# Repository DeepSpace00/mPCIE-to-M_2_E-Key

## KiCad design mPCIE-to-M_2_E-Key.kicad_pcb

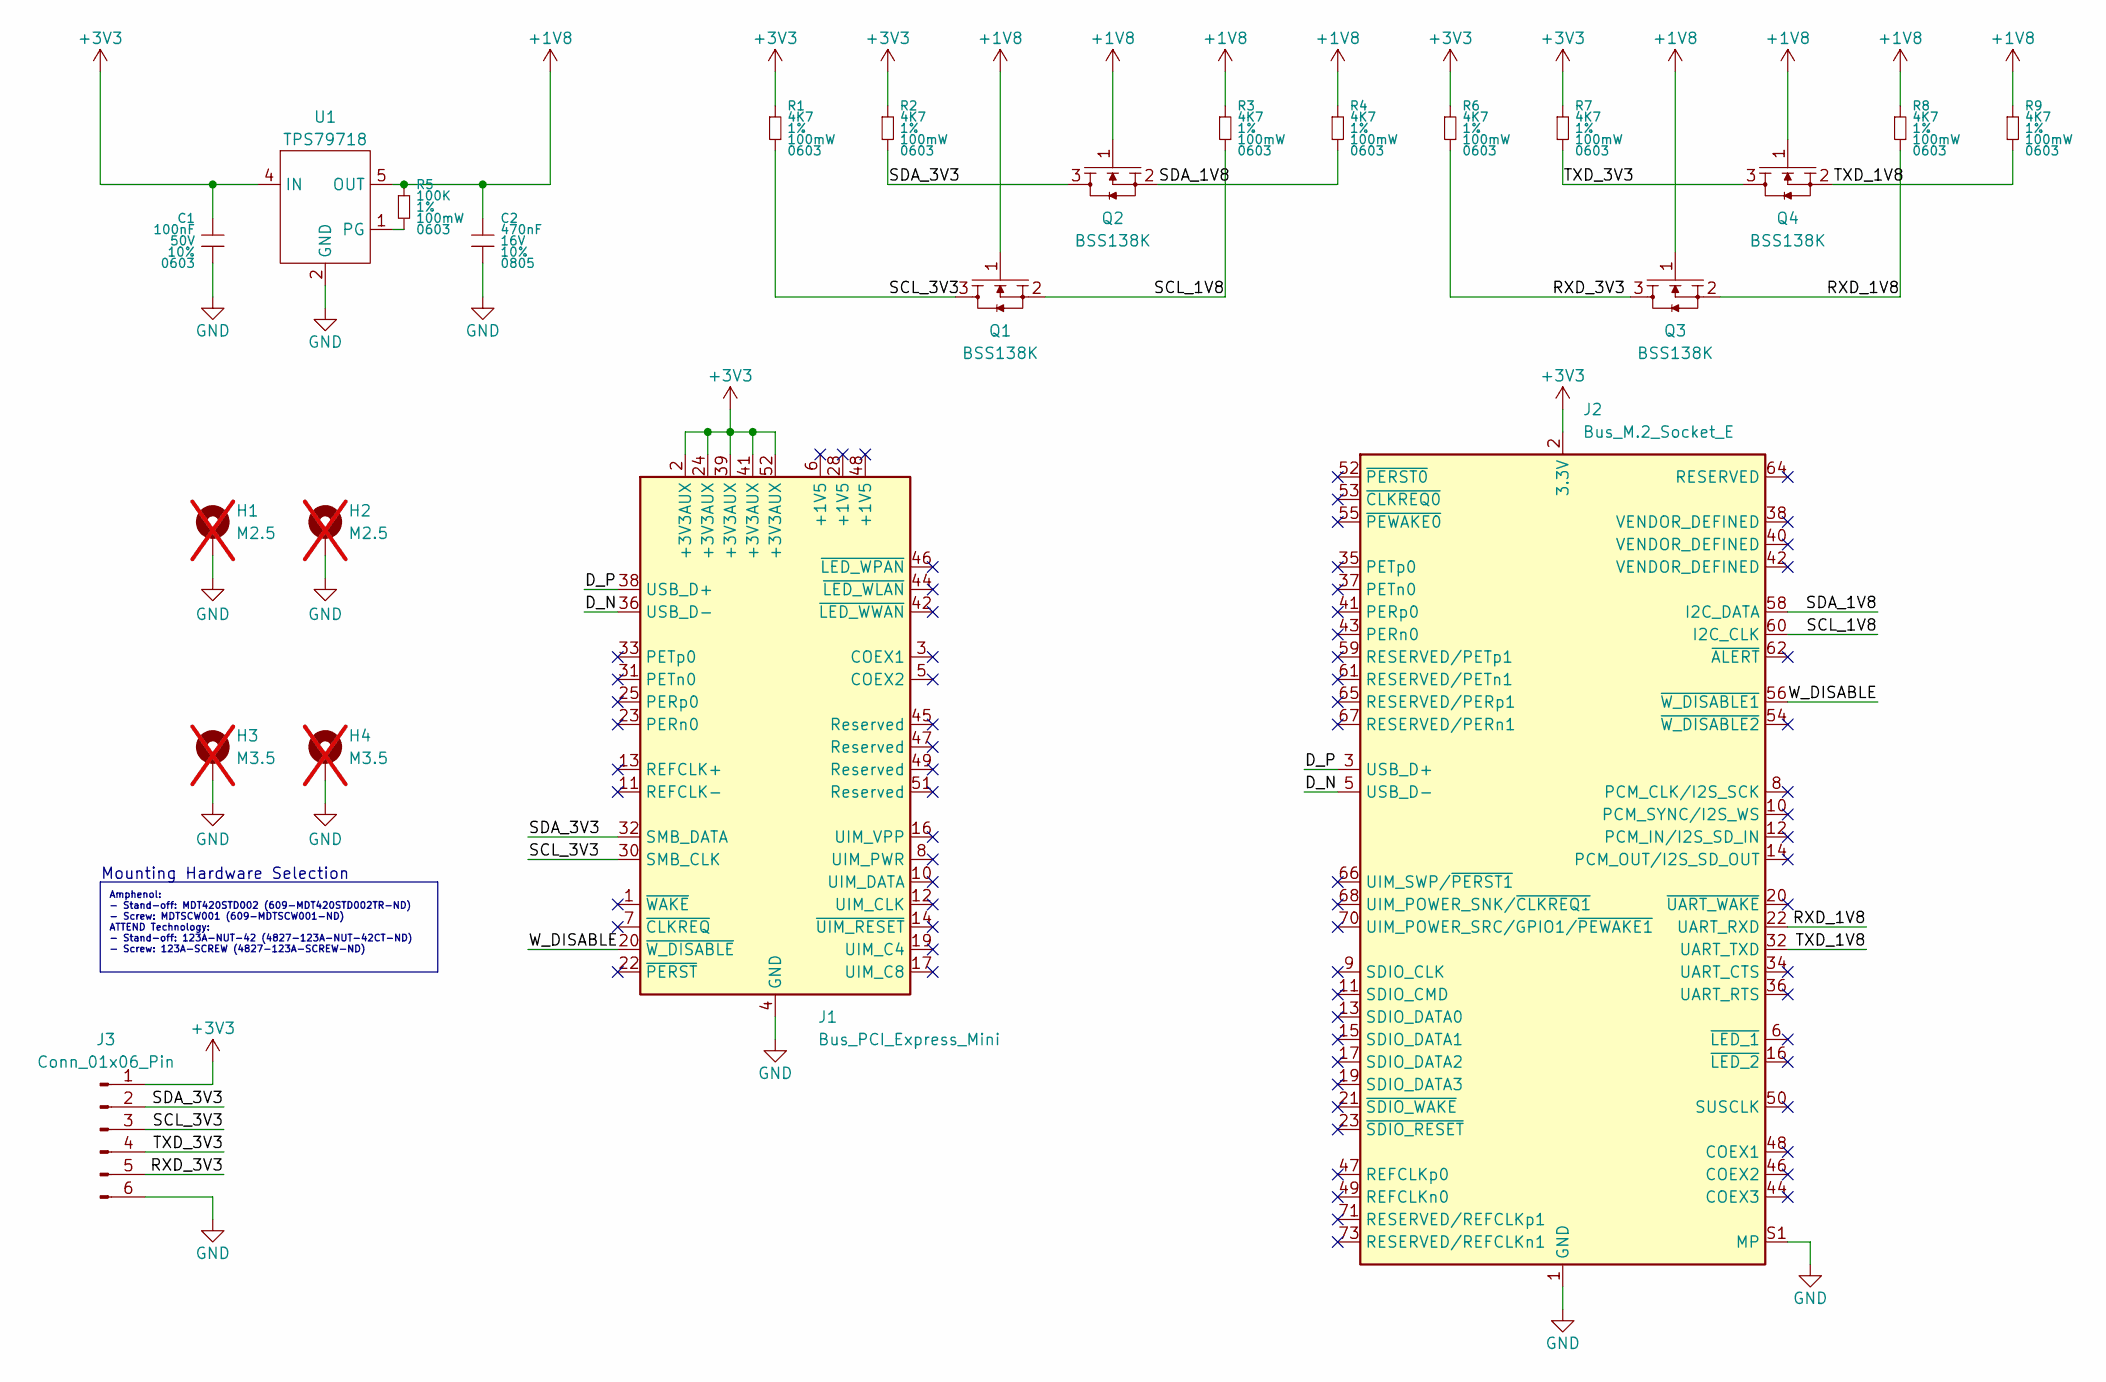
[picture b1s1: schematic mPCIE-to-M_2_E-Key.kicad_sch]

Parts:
C1: 100nF; MLCC0603; Tolerance 10%; Voltage Rating 50V; MPN 06035C104K4T4A
C2: 470nF; MLCC0805; Tolerance 10%; Voltage Rating 16V; MPN KAM21KR71C474KU
H1, H2: M2.5; M2.5_MH; not fitted
H3, H4: M3.5; MountingHole_3.5mm_Pad_Via; MPN MDT420STD002/123A-NUT-42; not fitted
J1: Bus_PCI_Express_Mini; BUS_mPCIe
J2: Bus_M.2_Socket_E; MDT420E01001; MPN MDT420E01001
J3: Conn_01x06_Pin; conn_01x06_254
Q1, Q2, Q3, Q4: BSS138K; SOT23-3P95_237X112L50X40N; MPN BSS138K-13
R1, R2, R3, R4, R6, R7, R8, R9: 4K7; CRCW0603; Tolerance 1%; Power Rating 100mW; MPN CRCW06034K70FKEA
R5: 100K; CRCW0603; Tolerance 1%; Power Rating 100mW; MPN CRCW0603100KJNEA
U1: TPS79718; SOT323-65P210X110-5; MPN TPS79718QDCKRQ1

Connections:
+1V8: C2.1, Q1.1, Q2.1, Q3.1, Q4.1, R3.1, R4.1, R5.1, R8.1, R9.1, U1.5 (OUT)
+3V3: C1.1, J1.2 (+3V3AUX), J1.24 (+3V3AUX), J1.39 (+3V3AUX), J1.41 (+3V3AUX), J1.52 (+3V3AUX), J2.2 (3.3V), J2.4 (3.3V), J2.72 (3.3V), J2.74 (3.3V), J3.1, R1.1, R2.1, R6.1, R7.1, U1.4 (IN)
/D_N: J1.36 (USB_D-), J2.5 (USB_D-)
/D_P: J1.38 (USB_D+), J2.3 (USB_D+)
/RXD_1V8: J2.22 (UART_RXD), Q3.2, R8.2
/RXD_3V3: J3.5, Q3.3, R6.2
/SCL_1V8: J2.60 (I2C_CLK), Q1.2, R3.2
/SCL_3V3: J1.30 (SMB_CLK), J3.3, Q1.3, R1.2
/SDA_1V8: J2.58 (I2C_DATA), Q2.2, R4.2
/SDA_3V3: J1.32 (SMB_DATA), J3.2, Q2.3, R2.2
/TXD_1V8: J2.32 (UART_TXD), Q4.2, R9.2
/TXD_3V3: J3.4, Q4.3, R7.2
/W_DISABLE: J1.20 (~W_DISABLE), J2.56 (~W_DISABLE1)
GND: C1.2, C2.2, H1.1, H2.1, H3.1, H4.1, J1.4 (GND), J1.9 (GND), J1.15 (GND), J1.18 (GND), J1.21 (GND), J1.26 (GND), J1.27 (GND), J1.29 (GND), J1.34 (GND), J1.35 (GND), J1.37 (GND), J1.40 (GND), J1.43 (GND), J1.50 (GND), J2.1 (GND), J2.7 (GND), J2.18 (GND), J2.33 (GND), J2.39 (GND), J2.45 (GND), J2.51 (GND), J2.57 (GND), J2.63 (GND), J2.69 (GND), J2.75 (GND), J2.S1 (MP), J2.S2 (MP), J3.6, U1.2 (GND)
unnamed: R5.2, U1.1 (PG)

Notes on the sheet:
Mounting Hardware Selection
Amphenol: - Stand-off: MDT420STD002 (609-MDT420STD002TR-ND) - Screw: MDTSCW001 (609-MDTSCW001-ND) ATTEND Technology: - Stand-off: 123A-NUT-42 (4827-123A-NUT-42CT-ND) - Screw: 123A-SCREW (4827-123A-SCREW-ND)

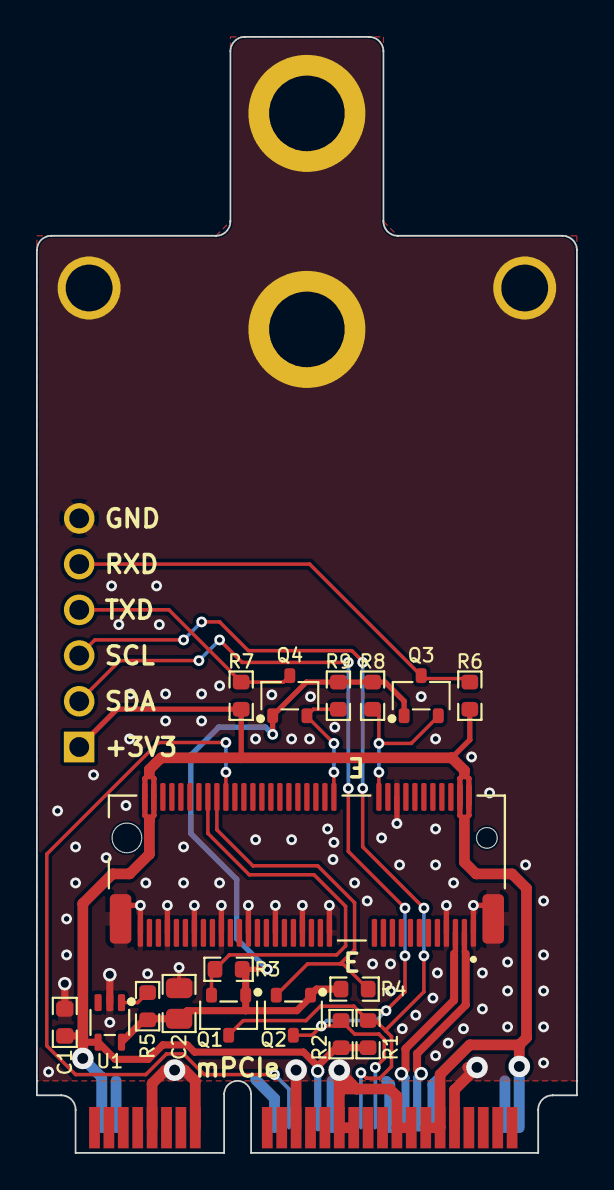
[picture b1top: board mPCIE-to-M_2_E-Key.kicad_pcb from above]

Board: 2 copper layers, 30.0 x 62.0 mm, 23 parts (0 on the bottom side), 15 nets.

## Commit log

2024-11-15 updated files
2024-11-22 fixed 1V8 reg DKPN
2025-03-15 added level shift and breakout for UART/I2C
